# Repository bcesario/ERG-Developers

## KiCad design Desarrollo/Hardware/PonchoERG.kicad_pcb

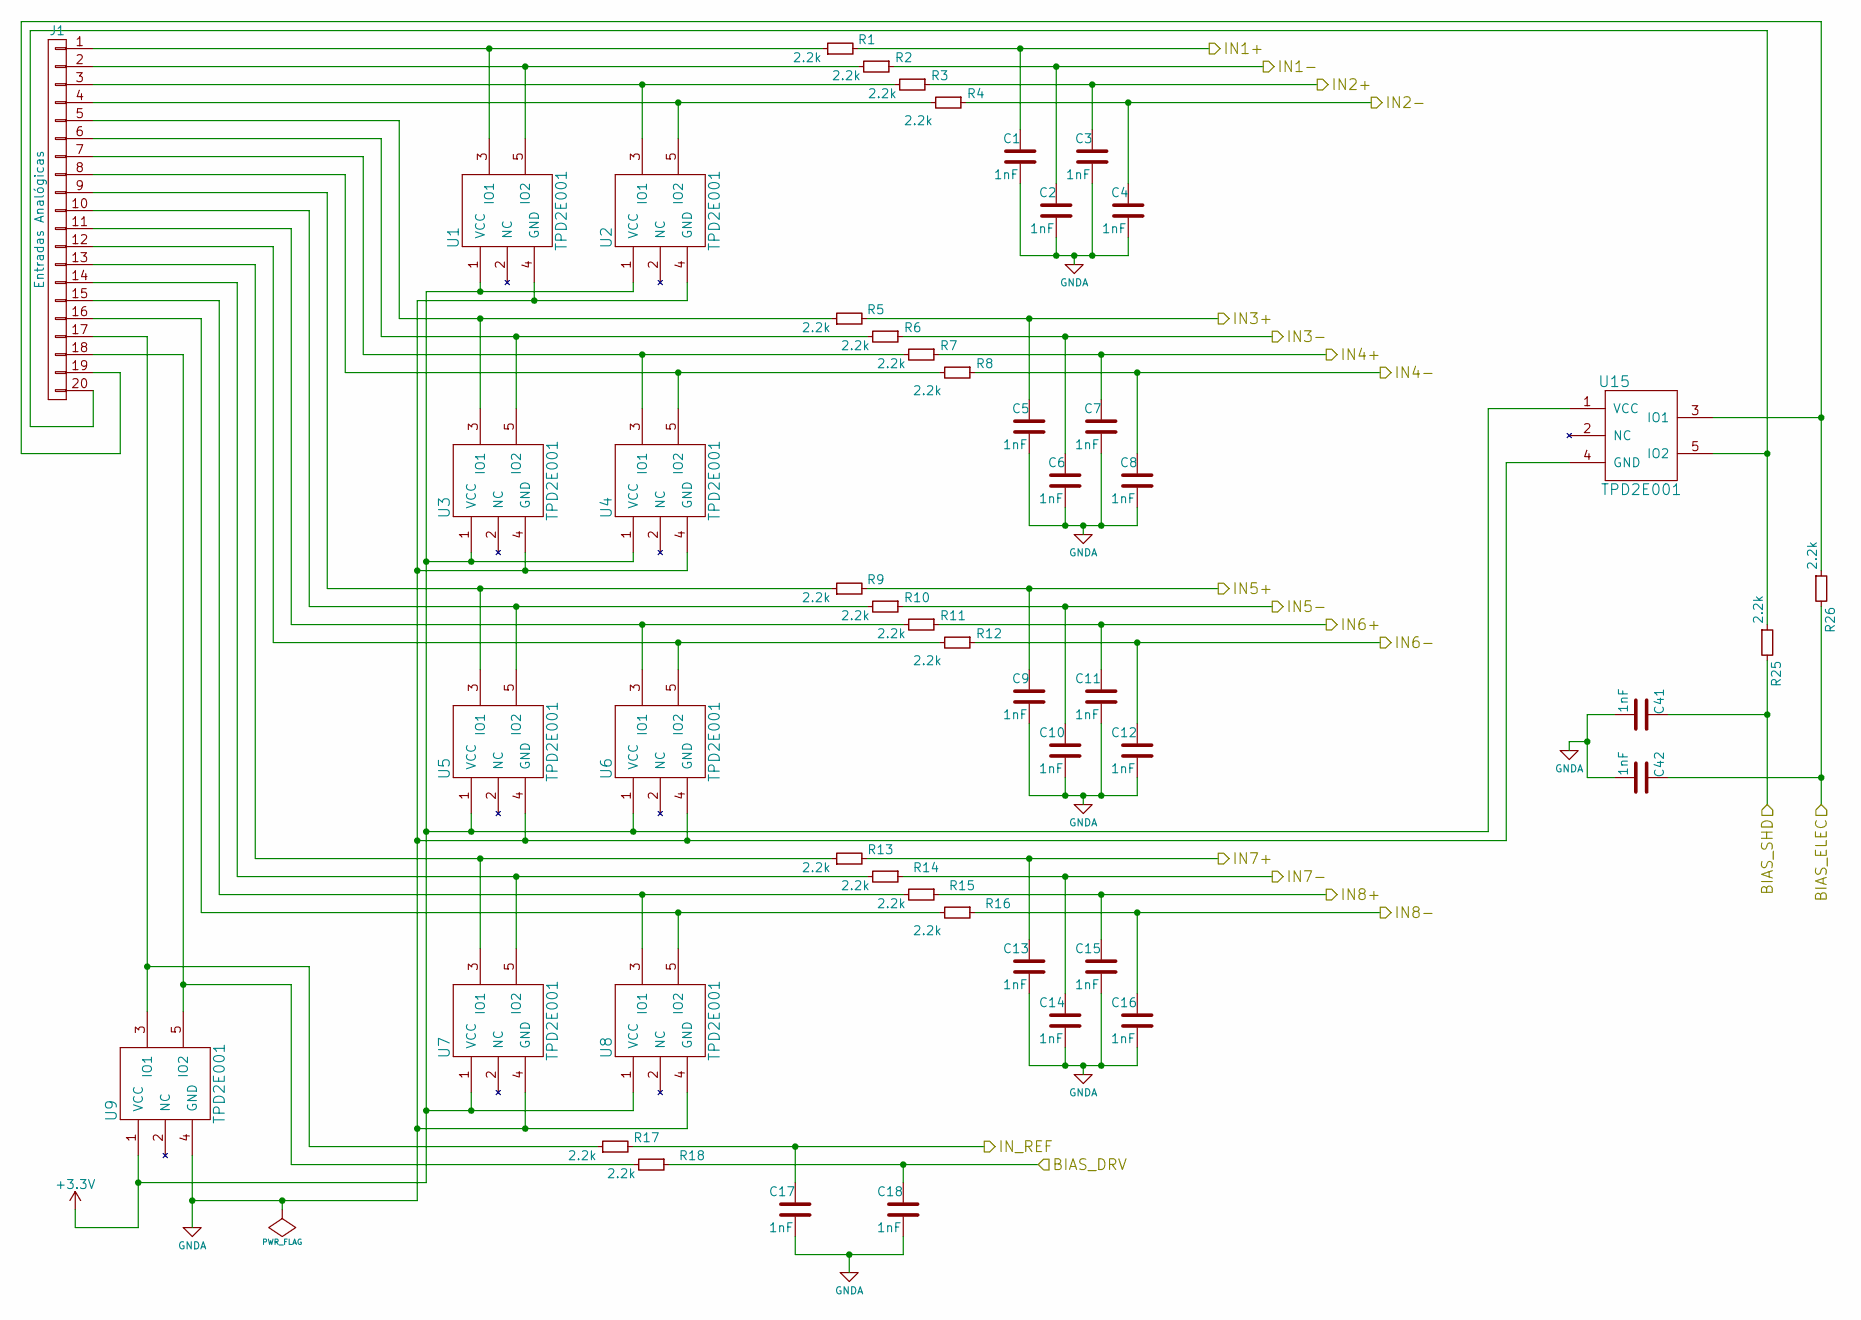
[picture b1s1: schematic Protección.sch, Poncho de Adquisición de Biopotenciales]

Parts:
C1, C2, C3, C4, C5, C6, C7, C8, C9, C10, C11, C12, C13, C14, C15, C16, C17, C18, C41, C42: 1nF; C_0805
J1: Entradas Analógicas; Pin_Header_Straight_1x20
R1, R2, R3, R4, R5, R6, R7, R8, R9, R10, R11, R12, R13, R14, R15, R16, R17, R18, R25, R26: 2.2k; R_0805
U1, U2, U3, U4, U5, U6, U7, U8, U9, U15: TPD2E001; SOT-23-5

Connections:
+3V3: U1.1 (VCC), U2.1 (VCC), U3.1 (VCC), U4.1 (VCC), U5.1 (VCC), U6.1 (VCC), U7.1 (VCC), U8.1 (VCC), U9.1 (VCC), U15.1 (VCC); also elsewhere on the board
/ADS1299/BIAS_DRV: C18.1, R18.1; also elsewhere on the board
/ADS1299/BIAS_ELEC: C42.1, R26.2; also elsewhere on the board
/ADS1299/BIAS_SHD: C41.1, R25.2; also elsewhere on the board
/ADS1299/IN1+: C1.1, R1.2; also elsewhere on the board
/ADS1299/IN1-: C2.1, R2.1; also elsewhere on the board
/ADS1299/IN2+: C3.1, R3.1; also elsewhere on the board
/ADS1299/IN2-: C4.1, R4.1; also elsewhere on the board
/ADS1299/IN3+: C5.1, R5.2; also elsewhere on the board
/ADS1299/IN3-: C6.1, R6.1; also elsewhere on the board
/ADS1299/IN4+: C7.1, R7.1; also elsewhere on the board
/ADS1299/IN4-: C8.1, R8.1; also elsewhere on the board
/ADS1299/IN5+: C9.1, R9.2; also elsewhere on the board
/ADS1299/IN5-: C10.1, R10.1; also elsewhere on the board
/ADS1299/IN6+: C11.1, R11.1; also elsewhere on the board
/ADS1299/IN6-: C12.1, R12.1; also elsewhere on the board
/ADS1299/IN7+: C13.1, R13.2; also elsewhere on the board
/ADS1299/IN7-: C14.1, R14.1; also elsewhere on the board
/ADS1299/IN8+: C15.1, R15.1; also elsewhere on the board
/ADS1299/IN8-: C16.1, R16.1; also elsewhere on the board
/ADS1299/IN_REF: C17.1, R17.2; also elsewhere on the board
GNDA: C1.2, C2.2, C3.2, C4.2, C5.2, C6.2, C7.2, C8.2, C9.2, C10.2, C11.2, C12.2, C13.2, C14.2, C15.2, C16.2, C17.2, C18.2, C41.2, C42.2, U1.4 (GND), U2.4 (GND), U3.4 (GND), U4.4 (GND), U5.4 (GND), U6.4 (GND), U7.4 (GND), U8.4 (GND), U9.4 (GND), U15.4 (GND); also elsewhere on the board
unnamed: J1.1, R1.1, U1.3 (IO1)
unnamed: J1.2, R2.2, U1.5 (IO2)
unnamed: J1.3, R3.2, U2.3 (IO1)
unnamed: J1.4, R4.2, U2.5 (IO2)
unnamed: J1.5, R5.1, U3.3 (IO1)
unnamed: J1.6, R6.2, U3.5 (IO2)
unnamed: J1.7, R7.2, U4.3 (IO1)
unnamed: J1.8, R8.2, U4.5 (IO2)
unnamed: J1.9, R9.1, U5.3 (IO1)
unnamed: J1.10, R10.2, U5.5 (IO2)
unnamed: J1.11, R11.2, U6.3 (IO1)
unnamed: J1.12, R12.2, U6.5 (IO2)
unnamed: J1.13, R13.1, U7.3 (IO1)
unnamed: J1.14, R14.2, U7.5 (IO2)
unnamed: J1.15, R15.2, U8.3 (IO1)
unnamed: J1.16, R16.2, U8.5 (IO2)
unnamed: J1.17, R17.1, U9.3 (IO1)
unnamed: J1.18, R18.2, U9.5 (IO2)
unnamed: J1.19, R26.1, U15.3 (IO1)
unnamed: J1.20, R25.1, U15.5 (IO2)

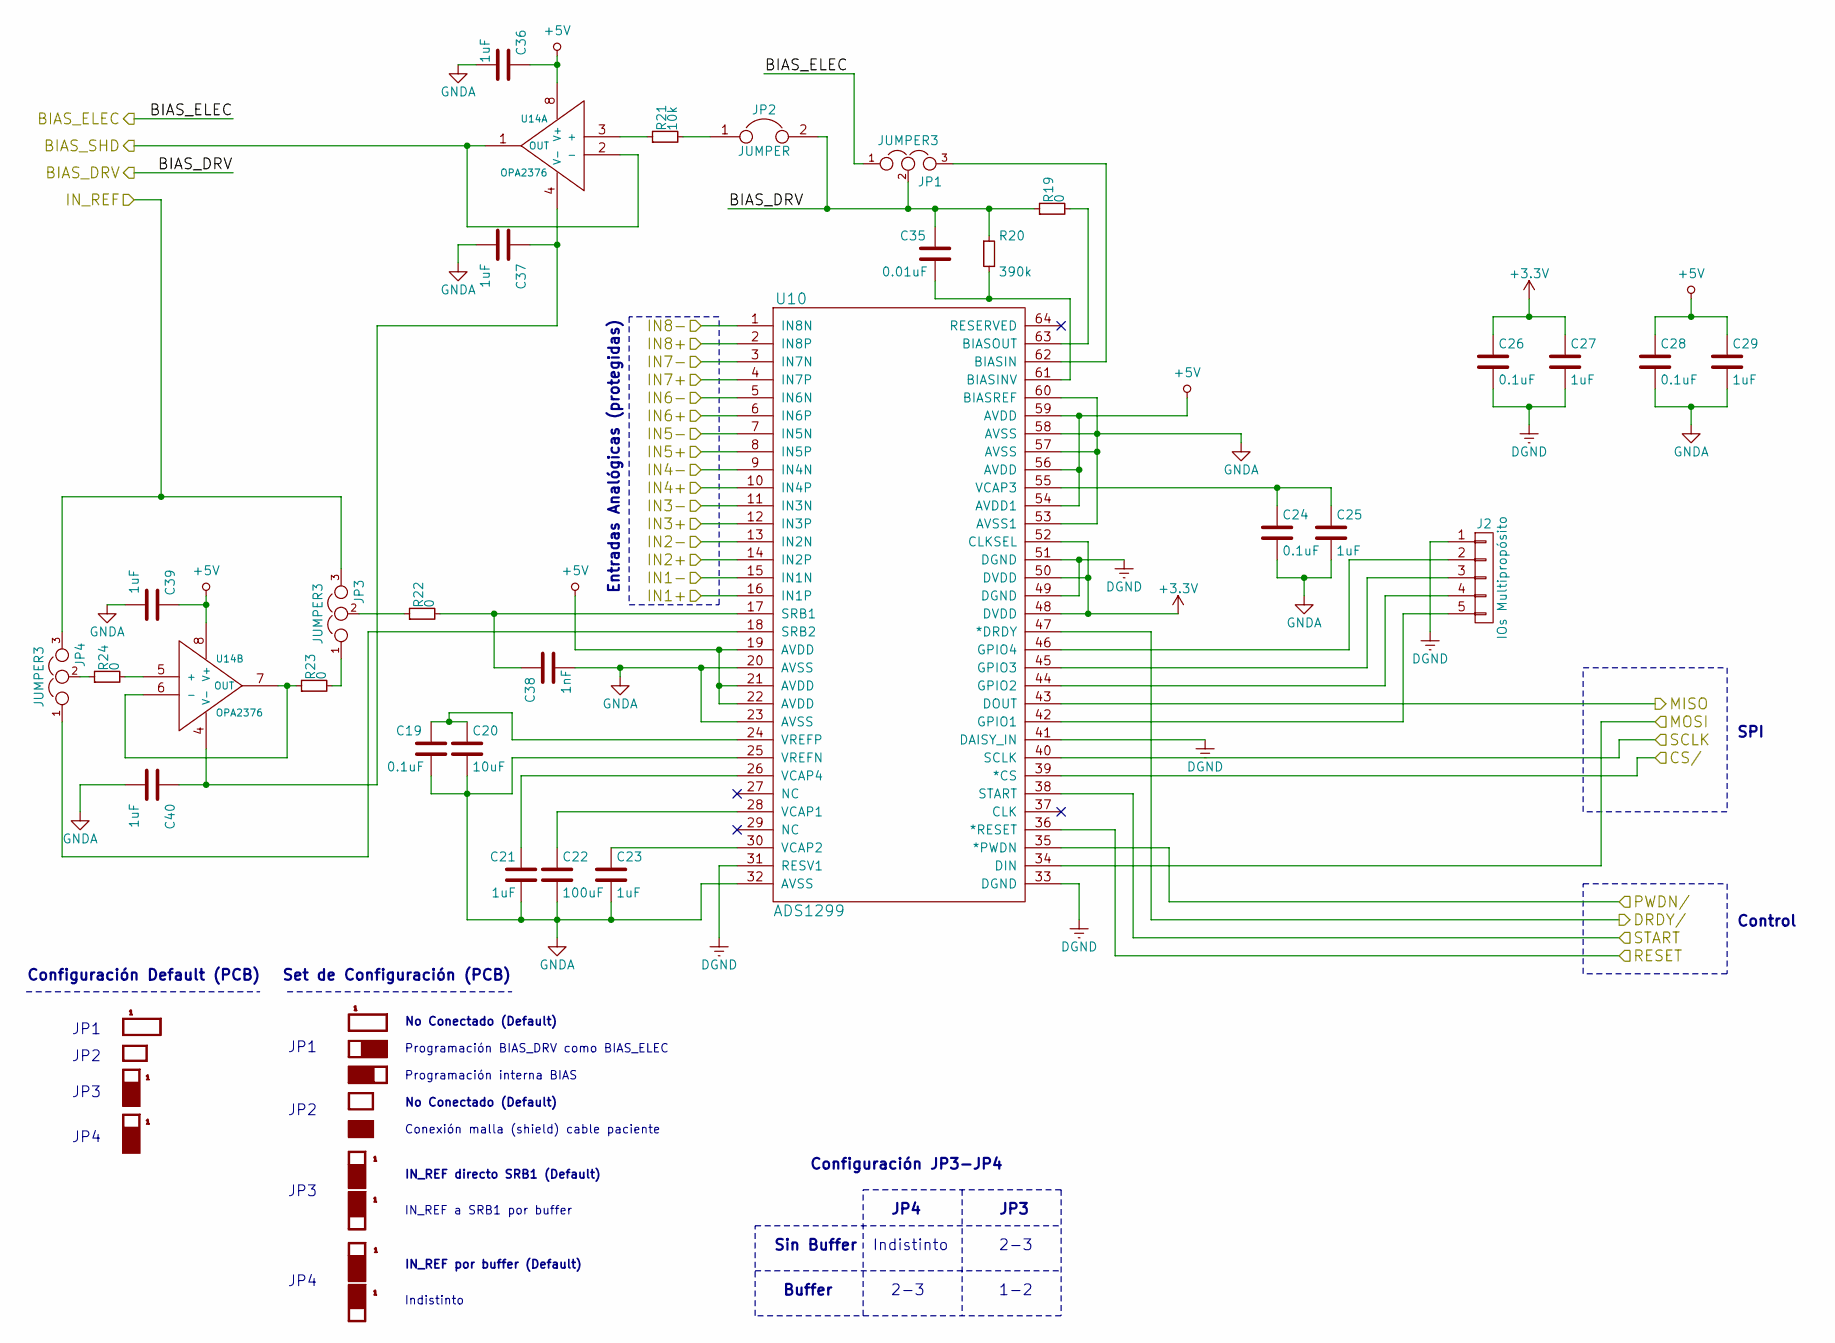
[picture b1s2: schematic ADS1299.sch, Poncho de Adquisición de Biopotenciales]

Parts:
C19, C24, C26, C28: 0.1uF; C_0805
C20: 10uF; C_0805
C21, C23, C25, C27, C29, C36, C37, C39, C40: 1uF; C_0805
C22: 100uF; C_1206
C35: 0.01uF; C_0805
C38: 1nF; C_0805
J2: IOs Multipropósito; Pin_Header_Straight_1x05
JP1, JP3, JP4: JUMPER3; Pin_Header_Straight_1x03
JP2: JUMPER; Pin_Header_Straight_1x02
Jumper_Config1: J_CFG; Jumpers_Default
Jumper_STD1: J_STD; Jumpers_Default
R19, R22, R23, R24: 0; R_0805
R20: 390k; R_0805
R21: 10k; R_0805
U10: ADS1299; TQFP-64_10x10mm_Pitch0.5mm
U14: OPA2376; SOIC-8-N

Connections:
+3V3: C26.1, C27.1, U10.48 (DVDD), U10.50 (DVDD), U10.52 (CLKSEL); also elsewhere on the board
+5V: C28.1, C29.1, C36.1, C39.1, U10.19 (AVDD), U10.21 (AVDD), U10.22 (AVDD), U10.54 (AVDD1), U10.56 (AVDD), U10.59 (AVDD), U14.8 (V+); also elsewhere on the board
/ADS1299/BIAS_DRV: C35.1, JP1.2, JP2.2, R19.1, R20.1; also elsewhere on the board
/ADS1299/BIAS_ELEC: JP1.1; also elsewhere on the board
/ADS1299/BIAS_SHD: U14.1 (OUT), U14.2 (-); also elsewhere on the board
/ADS1299/CS/: U10.39 (*CS); also elsewhere on the board
/ADS1299/DRDY/: U10.47 (*DRDY); also elsewhere on the board
/ADS1299/IN1+: U10.16 (IN1P); also elsewhere on the board
/ADS1299/IN1-: U10.15 (IN1N); also elsewhere on the board
/ADS1299/IN2+: U10.14 (IN2P); also elsewhere on the board
/ADS1299/IN2-: U10.13 (IN2N); also elsewhere on the board
/ADS1299/IN3+: U10.12 (IN3P); also elsewhere on the board
/ADS1299/IN3-: U10.11 (IN3N); also elsewhere on the board
/ADS1299/IN4+: U10.10 (IN4P); also elsewhere on the board
/ADS1299/IN4-: U10.9 (IN4N); also elsewhere on the board
/ADS1299/IN5+: U10.8 (IN5P); also elsewhere on the board
/ADS1299/IN5-: U10.7 (IN5N); also elsewhere on the board
/ADS1299/IN6+: U10.6 (IN6P); also elsewhere on the board
/ADS1299/IN6-: U10.5 (IN6N); also elsewhere on the board
/ADS1299/IN7+: U10.4 (IN7P); also elsewhere on the board
/ADS1299/IN7-: U10.3 (IN7N); also elsewhere on the board
/ADS1299/IN8+: U10.2 (IN8P); also elsewhere on the board
/ADS1299/IN8-: U10.1 (IN8N); also elsewhere on the board
/ADS1299/IN_REF: JP3.3, JP4.3; also elsewhere on the board
/ADS1299/MISO: U10.43 (DOUT); also elsewhere on the board
/ADS1299/MOSI: U10.34 (DIN); also elsewhere on the board
/ADS1299/PWDN/: U10.35 (*PWDN); also elsewhere on the board
/ADS1299/RESET: U10.36 (*RESET); also elsewhere on the board
/ADS1299/SCLK: U10.40 (SCLK); also elsewhere on the board
/ADS1299/START: U10.38 (START); also elsewhere on the board
DGND: C26.2, C27.2, J2.1, U10.31 (RESV1), U10.33 (DGND), U10.41 (DAISY_IN), U10.49 (DGND), U10.51 (DGND); also elsewhere on the board
GNDA: C19.2, C20.2, C21.2, C22.2, C23.2, C24.2, C25.2, C28.2, C29.2, C36.2, C37.2, C38.2, C39.2, C40.2, U10.20 (AVSS), U10.23 (AVSS), U10.25 (VREFN), U10.32 (AVSS), U10.53 (AVSS1), U10.57 (AVSS), U10.58 (AVSS), U10.60 (BIASREF); also elsewhere on the board
unnamed: C19.1, C20.1, U10.24 (VREFP)
unnamed: C21.1, U10.26 (VCAP4)
unnamed: C22.1, U10.28 (VCAP1)
unnamed: C23.1, U10.30 (VCAP2)
unnamed: C24.1, C25.1, U10.55 (VCAP3)
unnamed: C35.2, R20.2, U10.61 (BIASINV)
unnamed: C37.1, C40.1, U14.4 (V-)
unnamed: C38.1, R22.2, U10.17 (SRB1)
unnamed: J2.2, U10.46 (GPIO4)
unnamed: J2.3, U10.45 (GPIO3)
unnamed: J2.4, U10.44 (GPIO2)
unnamed: J2.5, U10.42 (GPIO1)
unnamed: JP1.3, U10.62 (BIASIN)
unnamed: JP2.1, R21.2
unnamed: JP3.1, R23.2
unnamed: JP3.2, R22.1
unnamed: JP4.1, U10.18 (SRB2)
unnamed: JP4.2, R24.1
unnamed: R19.2, U10.63 (BIASOUT)
unnamed: R21.1, U14.3 (+)
unnamed: R23.1, U14.6 (-), U14.7 (OUT)
unnamed: R24.2, U14.5 (+)

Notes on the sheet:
SPI
Entradas Analógicas (protegidas)
Control
Programación BIAS_DRV como BIAS_ELEC
Configuración Default (PCB)
JP1
JP2
JP3
JP4
Set de Configuración (PCB)
No Conectado (Default)
Programación interna BIAS
Conexión malla (shield) cable paciente
IN_REF directo SRB1 (Default)
IN_REF a SRB1 por buffer
IN_REF por buffer (Default)
Indistinto
2-3
1-2
Buffer
Sin Buffer
Configuración JP3-JP4

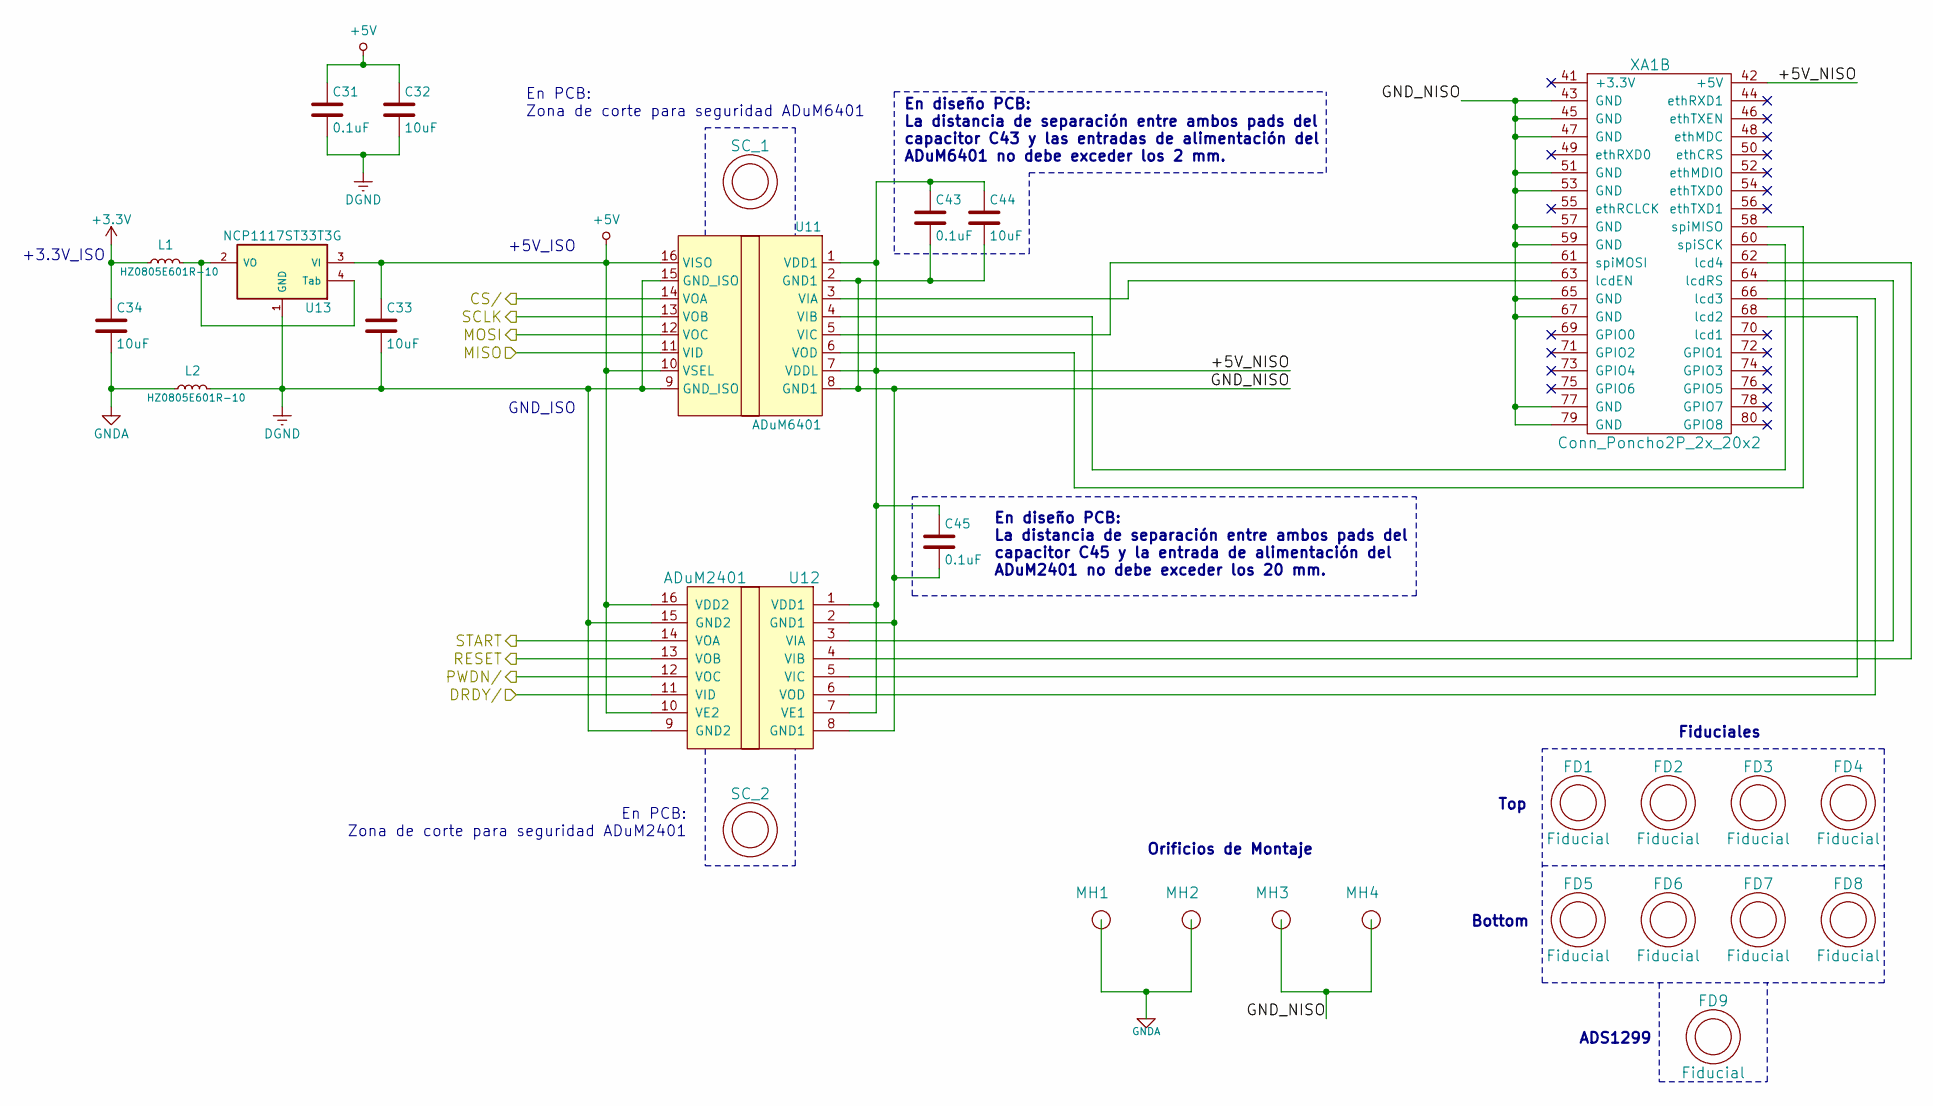
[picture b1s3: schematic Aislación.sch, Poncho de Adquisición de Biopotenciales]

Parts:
C31, C43, C45: 0.1uF; C_0805
C32, C33, C34, C44: 10uF; C_0805
FD1, FD2, FD3, FD4, FD5, FD6, FD7, FD8, FD9: Fiducial; Fiducial_1mm_Dia_2.54mm_Outer_CopperTop
L1, L2: HZ0805E601R-10; R_0805
MH1, MH2, MH3, MH4: PCB_HOLE; 1pin
SC_1: Slot_1; Fiducial_1mm_Dia_2.54mm_Outer_CopperTop
SC_2: Slot_2; Fiducial_1mm_Dia_2.54mm_Outer_CopperTop
U11: ADuM6401; SO-16-W
U12: ADuM2401; SO-16-W
U13: NCP1117ST33T3G; SOT-223
XA1: Conn_Poncho2P_2x_20x2; Conn_Poncho_Izquierdo

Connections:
+3V3: C34.1, L1.1; also elsewhere on the board
+5V: C31.1, C32.1, C33.1, U11.10 (VSEL), U11.16 (VISO), U12.10 (VE2), U12.16 (VDD2), U13.3 (VI); also elsewhere on the board
/ADS1299/CS/: U11.14 (VOA); also elsewhere on the board
/ADS1299/DRDY/: U12.11 (VID); also elsewhere on the board
/ADS1299/MISO: U11.11 (VID); also elsewhere on the board
/ADS1299/MOSI: U11.12 (VOC); also elsewhere on the board
/ADS1299/PWDN/: U12.12 (VOC); also elsewhere on the board
/ADS1299/RESET: U12.13 (VOB); also elsewhere on the board
/ADS1299/SCLK: U11.13 (VOB); also elsewhere on the board
/ADS1299/START: U12.14 (VOA); also elsewhere on the board
/AISLACIÓN/+5V_NISO: C43.1, C44.1, C45.1, U11.1 (VDD1), U11.7 (VDDL), U12.1 (VDD1), U12.7 (VE1), XA1.42 (+5V)
/AISLACIÓN/GND_NISO: C43.2, C44.2, C45.2, MH3.1, MH4.1, U11.2 (GND1), U11.8 (GND1), U12.2 (GND1), U12.8 (GND1), XA1.43 (GND), XA1.45 (GND), XA1.47 (GND), XA1.51 (GND), XA1.53 (GND), XA1.57 (GND), XA1.59 (GND), XA1.65 (GND), XA1.67 (GND), XA1.77 (GND), XA1.79 (GND)
DGND: C31.2, C32.2, C33.2, L2.2, U11.9 (GND_ISO), U11.15 (GND_ISO), U12.9 (GND2), U12.15 (GND2), U13.1 (GND); also elsewhere on the board
GNDA: C34.2, L2.1, MH1.1, MH2.1; also elsewhere on the board
unnamed: L1.2, U13.2 (VO), U13.4 (Tab)
unnamed: U11.3 (VIA), XA1.63 (lcdEN)
unnamed: U11.4 (VIB), XA1.60 (spiSCK)
unnamed: U11.5 (VIC), XA1.61 (spiMOSI)
unnamed: U11.6 (VOD), XA1.58 (spiMISO)
unnamed: U12.3 (VIA), XA1.64 (lcdRS)
unnamed: U12.4 (VIB), XA1.62 (lcd4)
unnamed: U12.5 (VIC), XA1.68 (lcd2)
unnamed: U12.6 (VOD), XA1.66 (lcd3)

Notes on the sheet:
+3.3V_ISO
+5V_ISO
GND_ISO
Fiduciales
Orificios de Montaje
Top
Bottom
ADS1299
En diseño PCB: La distancia de separación entre ambos pads del capacitor C43 y las entradas de alimentación del ADuM6401 no debe exceder los 2 mm.
En PCB: Zona de corte para seguridad ADuM2401
En PCB: Zona de corte para seguridad ADuM6401
En diseño PCB: La distancia de separación entre ambos pads del capacitor C45 y la entrada de alimentación del ADuM2401 no debe exceder los 20 mm.

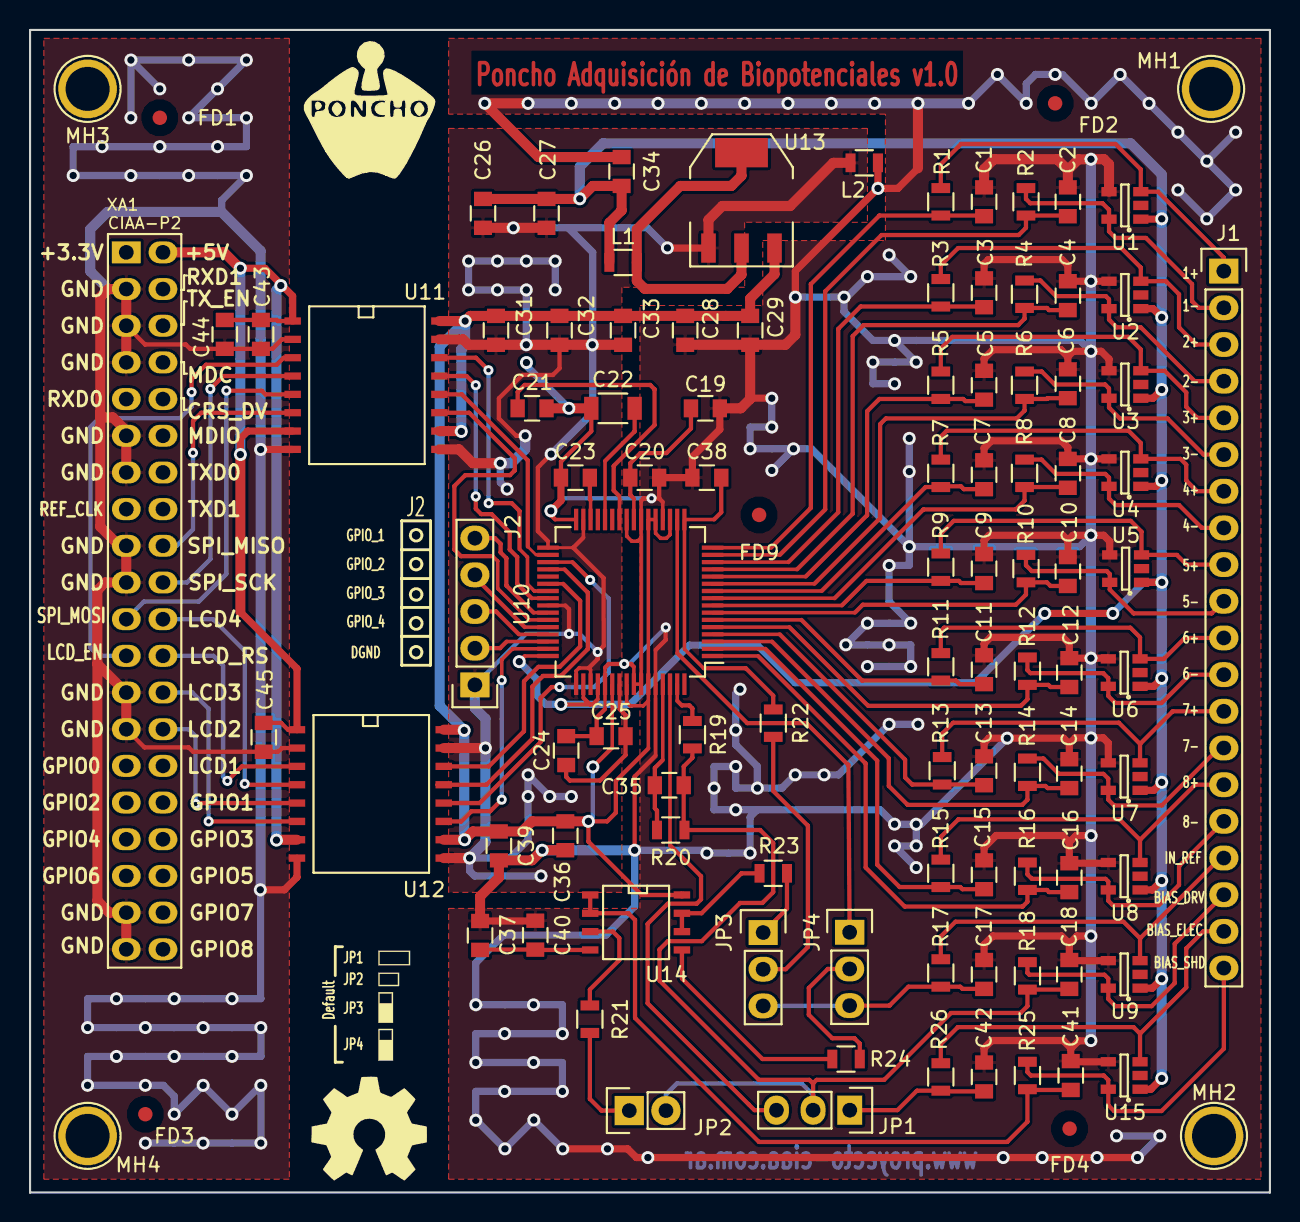
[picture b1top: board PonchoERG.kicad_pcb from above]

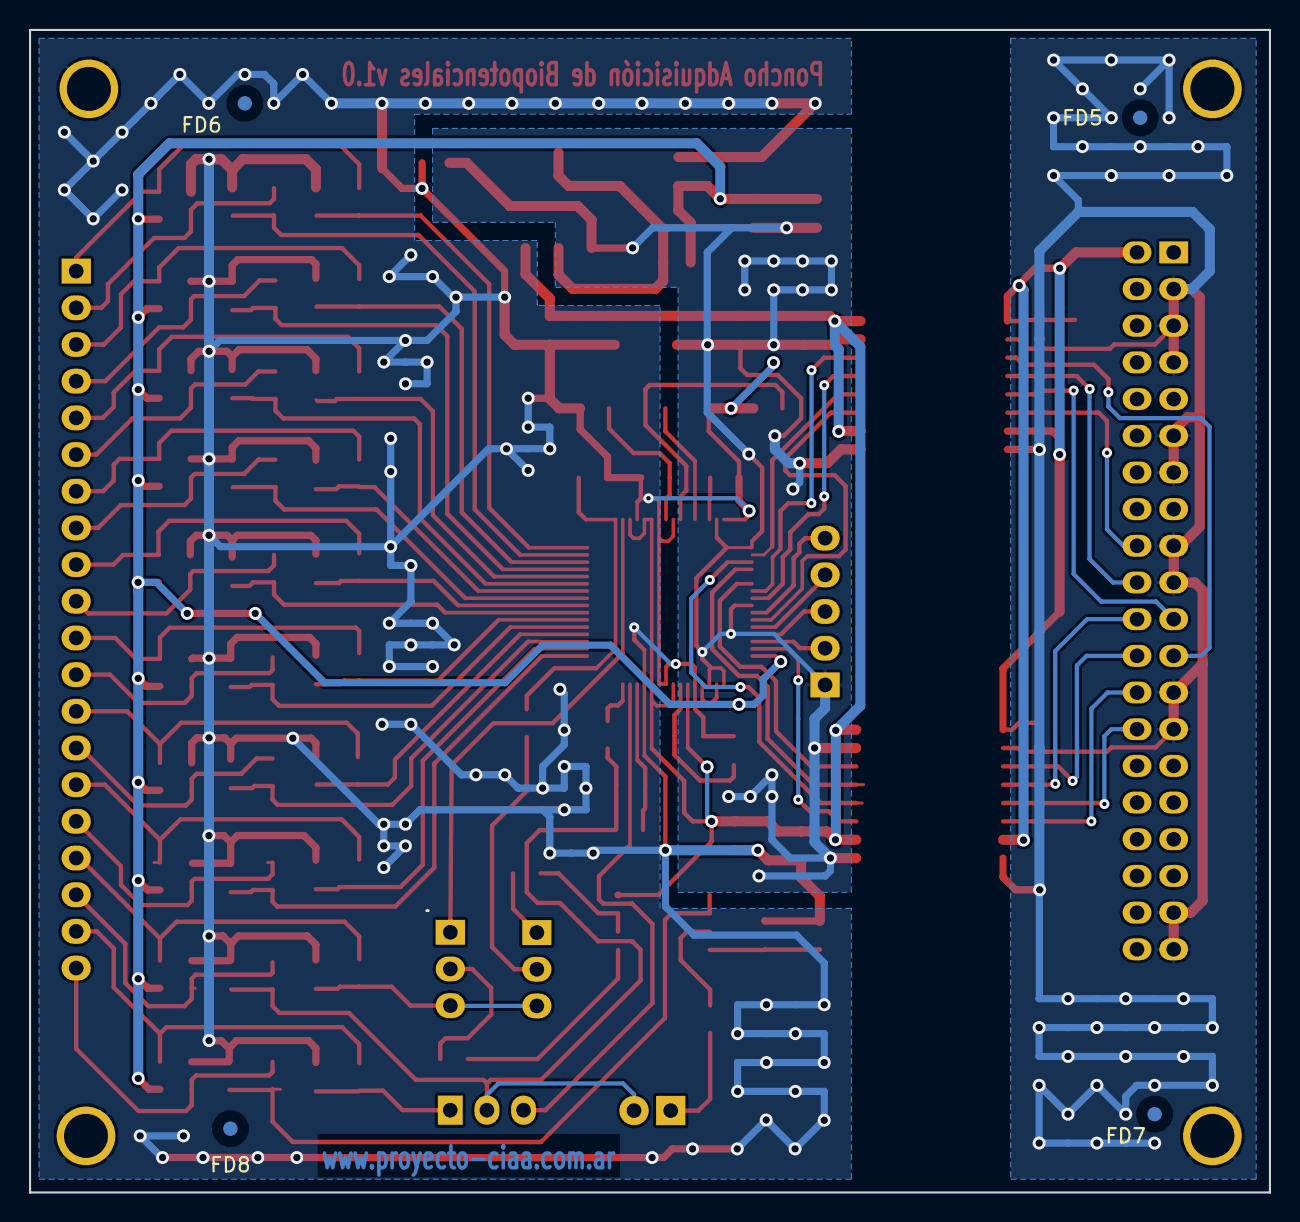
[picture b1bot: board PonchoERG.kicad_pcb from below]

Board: 2 copper layers, 85.9 x 80.5 mm, 111 parts (4 on the bottom side), 85 nets.

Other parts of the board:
G101: Logo_OSHWA

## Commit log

2016-08-30 Primer subida al repo del proyecto PonchoERG. Ya hay una primer versión de ubicación de componentes en el PCB.
2016-08-30 Actualización 1.0 - Inclusión de nuevos diodos de protección TPD2E001. - Creación de librería TPD2E001 y rediseño de esquemático. - Reubicación de componentes.
2016-09-02 Reubicación de ADS y componentes pasivos asociados. Sujeto a revisión.
2016-09-02 Subida n.0
2016-09-02 Comit irrelevante.
2016-09-02 Librerías pendiente de subida. OK.
2016-09-03 Manual del ADS1299
2016-09-03 Última actualización del proyecto. Creación de librería única "PonchoERG.lib" con todos los componentes. Se agregó el conector estilo CIAA para conectar SPI y alimentaciones. Se agregó carpeta con ar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
2016-09-05 Inclusión en esquemáticos de los nuevos bloques de circuitos para la utilización de las líneas del BIAS. Actualización de librería de proyecto. Objetivo de este comit: revisar actualización e inclusi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
2016-09-05 Actualización con recolocación de conector poncho izquierdo. Creación de directorios según requisito del Director. Orden de archivos y agregado de nuevos (datasheets, papers, imágenes, etc).
2016-09-05 pdf de la evaluation board puede servir como diseño de referencia
2016-09-06 Docs marcados con asuntos importantes
2016-09-07 Finalización de primer ruteo estimado. Revisión de cantidad de v
2016-09-07 Revert "Finalización de primer ruteo estimado. Revisión de cantidad de v"
    This reverts commit b379d941abb4cafe5355ba8bbe61a2a3831aeef6.
2016-09-07 Resubida de archivos actualizados por error en los DOS commits anteriores. Primer ruteo estimativo del PCB finalizado. Revisar posición de componentes y ruteo. Ver el POR QUÉ no se pueden conectar lo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
2016-09-08 Añadidura de zonas de aislación y separación de ZONA ISO y NO_ISO. Zonas de relleno de cobre finalizada. Ninguna (ni top ni bottom) se encuentran unidas a alguna red (ni de masa ni nada similar). Est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
2016-09-21 Última actualización de ruteo. Redimensión de placa. Cambio de ancho de algunas pistas. Cambio de componentes. Agregado de inductancias de aislación de masas y alimentación +5V.
2016-09-27 Mejora de ubicación de componentes y nuevo ruteo desde 0. Disminución notable de cantidad de vías. Diseño (casi) final. REVISAR.
2016-10-03 Actualización de esquemático, se completaron campos de "Hoja de dato" y "Código Digikey" para cada componente. Se completaron los rótulos de hojas. Versión Final de PCB. Actualización de tamaño de pi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
2016-10-04 Desarrollo de placa de driver para manejo de leds de estimulación visual. Creación de esquemático y PCB correspondiente.
2016-10-12 Revisión del SCH. Eliminación de JP5. Revisión de PCB y modificación de pistas basada en correción de errores del DRC. Se eliminaron todos los errores manteniendo el diseño. REVISAR. Además se quitar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
2016-10-15 Actualización final. Se añadieron dimensiones, referencias para ubicación correcta de ICs. Se añadieron vías nuevas entre planos top y bottom de masa (GNDA). REALIZAR REVISIÓN FINAL.
2016-10-22 Modificaciones basadas en nuevas revisiones. Se agregaron bypass en ADuMs. Inclusión de símbolos de "PONCHO" y "OPEN HARDWARE". Algunos cambios estéticos de pistas y otros funcionales. Unificación de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
2016-10-24 Actualización final con todas las revisiones corregidas. Realizar revisión FINAL.
2016-10-24 Nueva actualización. Intercambio de tierras GNDA por DGND en hoja esquemático "Aislación". Ídem en hoja de "Protección". Además se hizo visible el nombre de la tierra digital DGND que no figuraba. Re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
2016-10-27 Separación de planos de tierras DGND y GNDA. PCB Finalizado. REVISAR
2016-10-29 Actualización final. Serigrafía nueva de jumpers y logos que se habían borrado de PONCHO y OPEN HARDWARE. PLACA TERMINADA.
2016-10-29 Corrección de etiqueta de serigrafía en J2. Se cambió GPIO_3 que estaba repetido por GPIO_4.
2016-10-30 Actualización de PCB. Cotas de diseño. Generación de BOM. Archivos Gerber disponibles en carpeta "gerbers". Colocación de eje auxiliar de posicionamiento en mounting hole inferior izquierdo. Actualiz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
2016-10-30 Actualización de propiedades de 4 componentes en esquemático "Aislación.sch" y correspondiente generación de nueva BOM.
2017-08-14 Agregado de archivos de firmware completos en carpeta Firmware.
2017-12-14 - Actualización última versión de Firmware poncho biopotenciales. - Actualización librerías, footprints y otros en Hardware poncho biopotenciales.
